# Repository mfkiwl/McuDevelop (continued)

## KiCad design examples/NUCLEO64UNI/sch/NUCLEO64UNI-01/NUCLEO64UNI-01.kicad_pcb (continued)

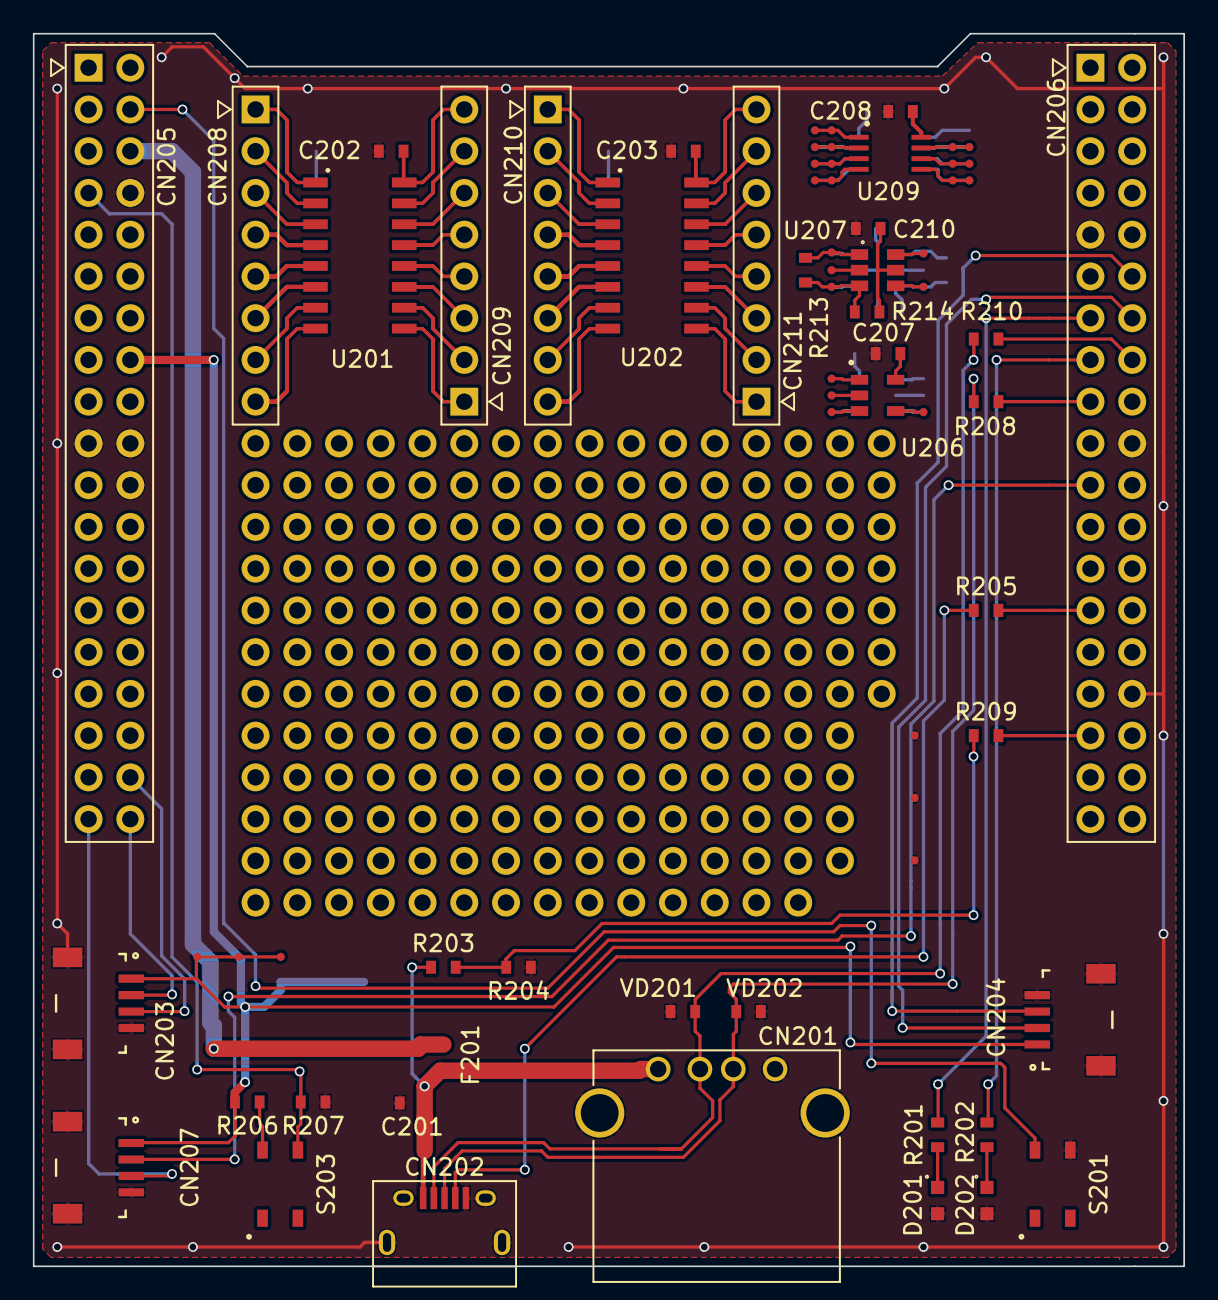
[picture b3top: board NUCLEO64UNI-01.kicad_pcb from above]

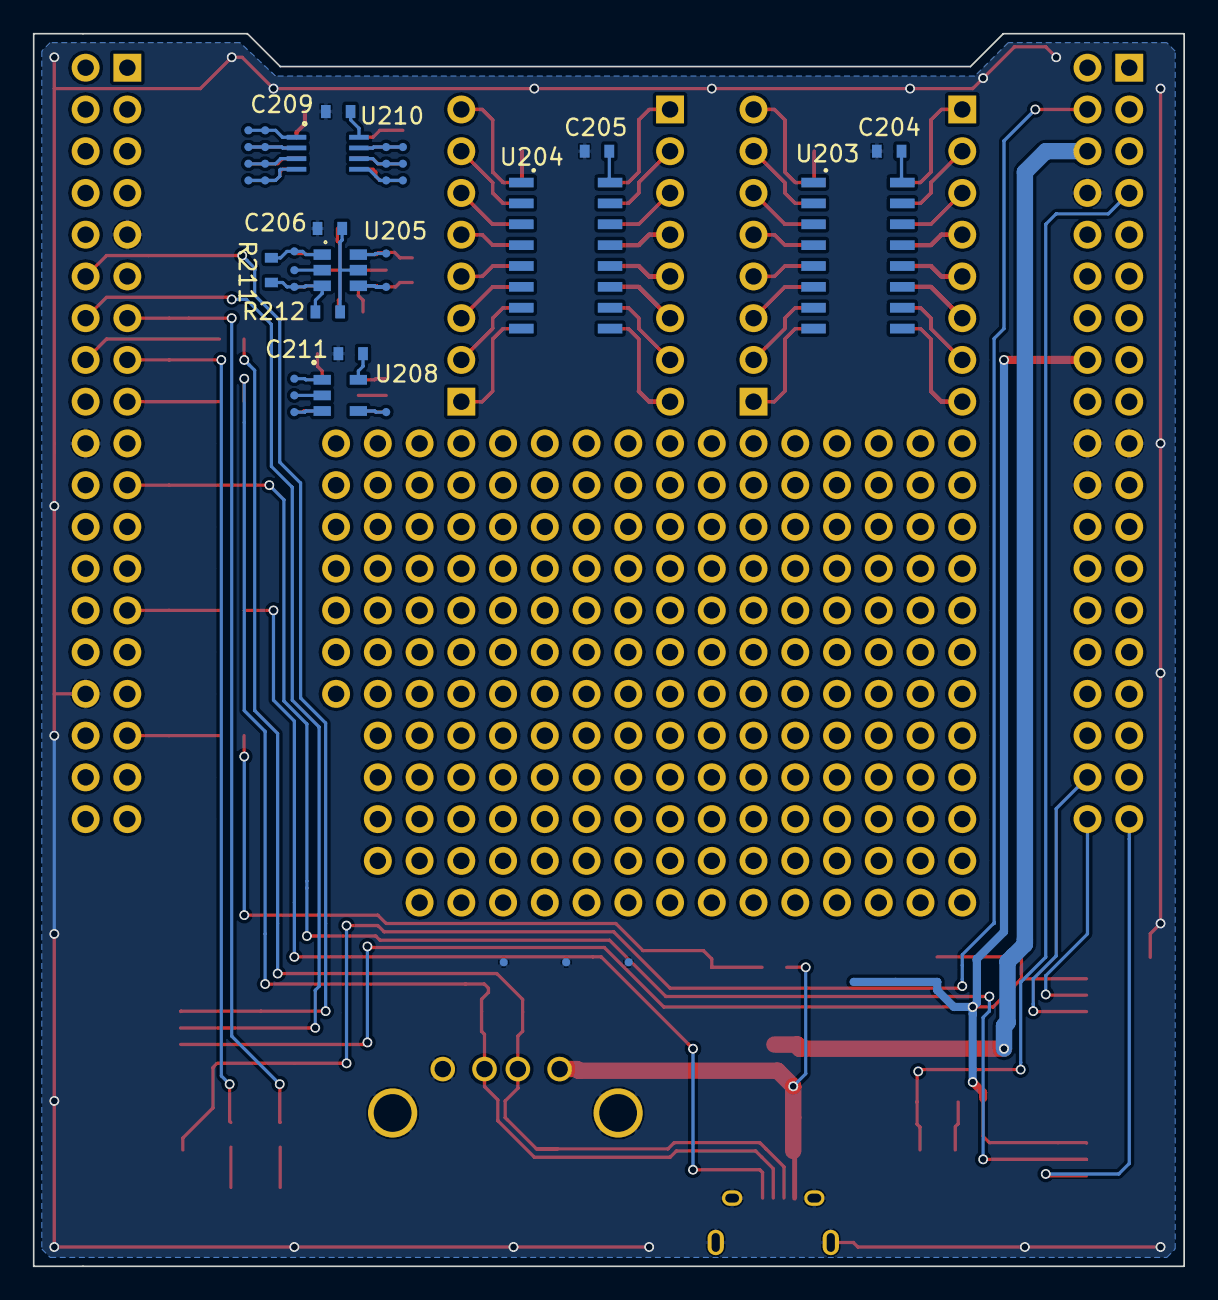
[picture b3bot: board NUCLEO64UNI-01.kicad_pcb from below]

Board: 2 copper layers, 70.0 x 75.0 mm, 111 parts (41 on the bottom side), 97 nets.

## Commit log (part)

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2019-01-25 CMSIS new
2019-01-25 Devices new
2019-01-25 Usbdif new
2019-01-25 0xff bintos.rb crc32.rb mot2bin.rb sconv.rb new
2019-01-26 boot/ Makefile boot1 boot2 new
2019-01-26 lib new
2019-01-27 STM32L0/Includexxxx deleted
2019-01-27 boot1/boot1.c boot2/main.c strProductText, strVersionText
2019-01-27 boot.mk boot.gcc.mk the path was changed
2019-01-27 mv boot/target .
2019-01-27 ctype_.c strtoul.c new copied from openbsd bionic
2019-01-27 boot.mk boot.gcc.mk the definitions were changed
2019-01-27 devUsb16.c DeInit()
2019-01-27 STM32/devFlash.[ch] new
2019-01-27 KICADKEY repository in McuDevelop/examples
2019-02-01 Makefile the TARGETCODE env is specified
2019-02-02 stm32l0.h stm32l4.h definition of SPI fifo exist or not
2019-02-02 devSpi16.c fifo use, if the device is STM32L4 not use, if the device is STM32L0 disable debug print
2019-02-02 devCounter.[ch] the funciton prototype of to get TIM CNT value was changed
2019-02-03 bmi160.h REG definitions
2019-02-03 bmi160.h REG definitons
2019-02-03 config version target name
2019-02-03 main.c the unit number of DevCounter() was used the through number
2019-02-07 devCounter.[ch] added new function DevCounterClearCounterValue() Init changed
2019-02-07 config USART BAUD MCO used
2019-02-07 system_STM32L0.c the LSI 37kHz clock out to MCO
2019-02-07 imu.c imu sampling rate was changed 1600Hz
2019-02-07 config version number
2019-02-08 bmi160.[ch] bmi160 access library
2019-02-08 Makefile imu.[ch] main.[ch] bmi160 access
2019-02-08 main.c ImuInit() is called with unit number from 0 to 3
2019-02-09 adxl345.[ch] adxl345 access
2019-02-10 adxl345.[ch] interrupt polarity bit
2019-02-10 imu.c mpu9250.[ch] new the mpu9250 driver was added
2019-02-10 adxl345.c bmi160.[ch] config CONFIG_IMU_RATE_XXX used for to change the imu sampling rate
2019-02-10 mpu9250.[ch] sampling setting
2019-02-11 IMUMB-01 schematics
2019-02-15 stm32l0.h main.[ch] command.c id get/set commands were added
2019-02-16 command.c command.txt main.c imu [num] get/set commands new
2019-02-17 stm32l0.h dma ch and request map for usart
2019-02-17 main.c imu.[ch] imu data is send with the tx dma printf() is not used
2019-02-22 devDma4.[ch] DevDmaClearIntr() new the return value of DevDmaIsFinished() was changed
2019-02-22 devSpi16.[ch] dma nonblock mode
2019-02-22 adxl345.[ch] bmi160.[ch] mpu9250.[ch] use spi nonblock with dma
2019-02-22 bmi160.[ch] main.[ch] use the spi dma nonblock
2019-02-23 intrvect.h the DMA handlers were registered
2019-02-23 config IMU debug IMU nonblock
2019-02-24 lis3dhh.[ch] new
2019-02-24 main.c 'o' is sent to uart, if the imu data was overwrite.
2019-02-24 Makefile imu.c lis3dhh routine was added text convert routine is coverted one by one, not used "for"
2019-02-24 thumb_case.S copied from https://chromium.googlesource.com/chromiumos/platform/ec/+/v1.9.0/core/cortex-m0
2019-02-24 main.c use volatile option to system1ms firm.gcc.mk gcc option -Os for speed instead of -O0
2019-02-24 gpio.imu4p.h SWD debug option
2019-03-01 bmi160.c lis3dhh.c mpu9250.[ch] the read data is copied to structure by each 16bit etc
2019-03-01 imu.c imu.h reduce output text raw buffer was moved after cnt(32bit) for 32bit align
2019-03-01 stm32l0.h the count of the usart modules
2019-03-01 devDma4.[ch] DevDmaInitAddrSize() new the dma is not started, if only call Init(), but the dma is stared if Start() is called
2019-03-01 devUsart.[ch] DevUsartIsSendingDma() DevUsartSendStopDma() new
2019-03-02 adxl345.[ch] bmi160.[ch] imu.[ch] lis3dhh.[ch] main.c mpu9250.[ch] firm.ld heap size was changed the local buffer is gotten by malloc the driver is call with imuHandler_t ptr instead of unit
2019-03-02 config SPI nonblock
2019-03-03 imu.[ch] main.[ch] the bianry imu data with hamming coding
2019-03-03 checkImu.rb check the imu data (text, hamming coding)
2019-03-15 adxl345.c bmi160.c lis3dhh.c mpu9250.c imu.h new member capability was added
2019-03-15 devUsart.c recv method is only pio
2019-03-15 devCrc.[ch] new
2019-03-15 system_STM32L0.c MCO is output 1MHz which is generated by HSI 16MHz
2019-03-15 hamming.rb additional parity
2019-03-15 config version
2019-03-20 imu.c temperature range was changed val16 variables
2019-03-21 devUsart.[ch] fifo recv main.[ch] do not send echo char
2019-03-21 devUsart.[ch] recv with dma DevUsartInterruptDmaRecv() DevUsartInterruptDmaSend() new
2019-03-22 command.c, .txt imu [num] regset new
2019-03-22 checkImu.rb the "start" command is sent before check "start" "stop# command enable bit
2019-03-23 command.c main.[ch] spi speed was changed 8MHz imu [num] regget command capture enable/disable the spi read is changed to the blocking read
2019-03-23 devSpi16.c the rx buffer is flushed only 1 byte, if the fifo is not supported RXONLY bit is clear at a time when SPE is clear
2019-03-23 command.c version text
2019-03-23 IMUBM-01.pdf new
2019-03-23 imu4p.doc.odt, .pdf new
2019-04-09 NUCLEO64UNI-01.pro, sch, kicad_pcb new
2019-04-09 010.sch new
2019-04-16 mpu9250.[ch] the device id of TDK/Invensense products were added prepare to probe ICM20789
2019-05-09 icm42605.[ch] add the TESTID definition was added
2019-06-09 Makefile prog entry uses dfu-util
2019-07-07 USBSOFIC-1.kicad_pcb USBSOFIC-1.pro outline gerber is out
2019-07-07 USBSOFIC-1.pdf update pdf
2019-07-07 IMU4P firm.ld the flash and ram area were changed
2019-07-07 stm32l4Flash.h NO_PECR definition
2019-07-07 stm32Otg.h stm32h7.h Otg reg definitions
2019-07-07 stm32 devFlash.c use FLASH_NO_PRGKEYR FLASH_NO_PECR definitions
2019-07-07 devDma4.c CSELR
2019-07-07 stm32Spi16.h I2S definitions
2019-07-07 stm32f7.h stm32f7Flash.h stm32f7Pwr.h stm32F7Rcc.h new
2019-07-14 devUsart.[ch] stm32f7.h change the RX bit definitions for STM32F7
2019-07-14 start_gcc.s the interrupt vector is also enable for M7
2019-07-14 USBSOFIC/subcpu new
2019-07-21 devI2c.c I2Cx_NUM definitions the SEQ_SEND_CMD is not set to the sequence variable
2019-07-21 stm32f7Rcc.h OTGHSULPIEN USBHSEN
2019-07-27 si5351.[ch] new
2019-07-28 Makefile the debug print is disable at programming
2019-07-28 config HSE clock was changed 24MHz SI5351 i2c addr
2019-07-28 gpio.usbsofic.h the I2C port was changed
2019-07-28 firm/Makefile main.[ch] usb_desc.h system.[ch] OSC[26MHz] -- SI5351[24MHz] -- STM32F730 working the no-used usb if nums were deleted the usbphy pll was maybe working
2019-09-30 stm32sdmmc.h new
2019-09-30 FPGACONF/sch *.sch FPGACONF-cache.lib -rescue.lib .kicad_pcb .net .pro .sch
2019-10-12 Fatfs new R0.13c
2019-10-12 ff.[ch] add the patchs ff13c_p[12345].diff
2019-10-14 STM32/src/devError.h deleted
2019-10-14 diskio.c deleted
2019-10-30 strtok.c strcmp.c bionic-fe6338d-libc-string
2019-11-02 pcb (-01) files were moved to FPGACONF-01
2019-11-02 FPGACONF.pdf, .pdf.xoj new
2019-11-03 STM32/src devSdmmc.[ch] new only pio
2019-11-03 stm32f7Rcc.h stm32f7Pwr.h bit definitions
2019-11-03 devGpio.h value for the function of SDMMC and USBHS
2019-11-03 stm32Spi16.h SPI_CR1_BR_VAL(x) was added
2019-11-03 stm32Gpio.h the func 12 number was defined
2019-11-03 def.mk SDMMC, FATFS, LLVM dir path definitions
2019-11-03 firm.mk .S make rule
2019-11-03 FPGACONF main source
2019-11-03 FPGACONF config target.conf new
2019-11-03 config config for FPGACONF STM32F730
2019-11-03 stm32Dma.h new
2019-11-03 stm32Fmc.h new
2019-11-03 arm/aeabi_ldivmod.S arm/aeabi_uldivmod.S divdi3.c divmoddi4.c udivmoddi4.c new
2019-11-03 int_lib.h types.h util.h new
2019-11-03 int_endianness.h new
2019-11-03 stm32l0.h DMA, USART definitions for STM32L0
2019-11-03 stm32l0.h SpiNo_t new
2019-11-03 Makefile memcmp.c was deleted to compile
2019-11-03 Makefile deleted -DULONG_MAX=UINT32_MAX moved to mk/firm.mk
2019-11-03 lib/openbsd/include.ext new
2019-11-03 devUsart.c the prototype of fifo.c was changed
2019-11-09 firm.mk armclang env
2019-11-09 stm32Dma7.h new
2019-11-09 devDma7.[ch] new
2019-11-09 devSdmmc.[ch] sdmmc.c dma read (not yet) ioctl transfer info write function is NOT ready
2019-11-09 stm32f7.h dma header
2019-11-09 firm.ld the heap snd tack size were changed
2019-11-09 main.[ch] FMC clock setting, stack size fpgaconf.[ch] fmc dma sending, double buffer, 32kB buffer system.[ch] the cpu clock was set 200MHz, malloc() uses the rtos config cpu clock 200MHz Makefile rem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
2019-11-10 system.c the memory is gotten from the freertos
2019-11-10 config version, target name
2019-11-10 FPGACONF.pdf.xoj disable the cs sel ecp5 eva board sw1 descriptions
2019-11-16 USBSOFIC: FreertosConfig.h the stack size was changed
2019-11-16 start_gcc.s SystemInit() call was moved in main.c
2019-11-16 FPGACONF.pin.ods changed
2019-11-16 devDma4.c devUsart.c DevDmaGetTransferedCount() new
2019-11-16 stm32f7Rcc.h the number of OTGFSEN bit was changed 7
2019-11-16 stm32Otg.h otg bit definitions
2019-11-16 stm32Usbphyc.h LDO_ENABLE definitons
2019-11-16 usbdaudio.h defined the audio sampling frequency
2019-11-16 USBSOFIC: main.c the stack size of main task was changed 0x1000 the os stack print was added, howevery disable SystemInit() was moved from start_gcc.s the Usbdcore entries were set to devUsb() USB_HS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
    FreeRtosConfig.h
    stack size debug print
    the os heap size was changed 0x8000
    config
    non boot loader setting (adhoc)
    the cpu and the bus clock was changed
2019-11-16 stm32h7Rcc.h USART1EN,USART6EN definitions
2019-11-24 stm32AdcF730.h devAdcF730.[ch] new
2019-11-24 stm32f7.h stm32f7Rcc.h adc definitions tim8 definitions
2019-12-01 config system.[ch] malloc method (heap or rtos)
2019-12-01 sdmmc.[ch] OCR,SCR,CSD,CID details print
2019-12-10 devErrono.h WOULDBLOCK
2019-12-10 devSdmmc.[ch] usr interrupt call back, if cb is set and finish recv sdmmc.[ch] Rtos event but not used yet Callback()
2019-12-10 fpgaconf.c use the recv done interrupt the postion of calling MainInitSdmmc() was changed main.c deleted the un-used codes config intrrupt enable/disable macro CONFIG_SDMMC_MIDDLE_USE_RTOS was added
2019-12-28 config sdmmc sleep definition
2019-12-28 fpgaconf.c f_mount is called with 0 (no initialize)
2020-01-03 system.c added the rtos.h
2020-01-03 rtos.[ch] the interrupt priority definitions were changed parameter set (however not used)
2020-01-04 config CONFIG_SDMMC_MIDDLE_USE_RTOS set 0
2020-01-04 sdmmc.c use the RTOS sleep
2020-01-19 FPGACONF-02 schematics support for SD-DDR (H743) test
2020-01-19 FPGACONF-02 pcb support for the SD-DDR test
2020-04-12 devI2c.[ch] DevI2cScan() new add the timeout
2020-04-12 devI2c.[ch] DevI2cWaitISR() new modify TransmitPio() routine
2020-07-04 Devices/STM32/src/devUsb320a.[ch] disable the phy code , if not have
2020-07-04 lib/common/rtos.h the priority value was changed
2020-07-04 Devices/STM32H7/include/stm32h7.h module definitions Devices/STM32/include/stm32Usbphyc.h address offset Devices/STM32/include/stm32Otg.h ULPIAR definitions were added
2020-09-21 devFlash.[ch] devFlashF73x.c available to burn to STM32F733 flash
2020-09-21 STM32F7/include/stm32f7Flash.h OPTKEY definition
2020-09-21 lib/common/start_gcc.s remove the .if condition
2020-09-21 McuDevelop/examples/BootSTM32F73x target/STM32F7/boot2/update.c address check target/STM32F7/config Firmware start address
2020-09-21 lib/common/start_gcc.s check the NO_VECTOR
2020-09-27 Devices/STM32/src/devFlash.h added the prototype DevFlashEraseChip() Devices/STM32/src/devSdmmc.c remove indclude
2020-09-27 Middlewares/Sdmmc/src/sdmmc.c remove #if 1 and the debug print
